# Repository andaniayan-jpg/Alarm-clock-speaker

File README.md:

- This is a custom alarm clock made using a microcontroller, an OLED display, and a rotary encoder.
- The clock allows setting and controlling alarms using the rotary encoder instead of buttons.
- The project includes a custom PCB, 3D-printed enclosure, and firmware.
- I wanted to learn how to design a complete hardware project from scratch.
- I wanted to understand how PCB design, enclosure design, and firmware work together.
- I also wanted to learn how to fix real-world problems like connector height and component placement.
This project is a custom-built alarm clock designed using a microcontroller, an OLED display, and a rotary encoder for user interaction. I created it to learn how a complete hardware project comes together,from PCB 
design and enclosure CAD to basic firmware. While building it, I had to solve practical problems like display mounting height, connector placement, and enclosure fit, which helped me understand real-world hardware
constraints. All design files and code are included so the project can be recreated or modified.

BOM ( bill of materials ), with quantity
1. XIAO ESP32-C3 (1)
2. OLED Display 128x64 (I2C) (1) 
3.  Rotary Encoder (1)
4.  Push Buttons (1)
5.  Speaker-CUI Devices CMR-1206S-67-1 (1)
6.  Battery Holder (1)
7.  Resistors (5)
8.  Capacitors (5)
9.  Custom PCB (1)
   THE FULL LIST OF COMPONENTS WITH PRICE AND QUANTITY IS IN BOM.csv file.

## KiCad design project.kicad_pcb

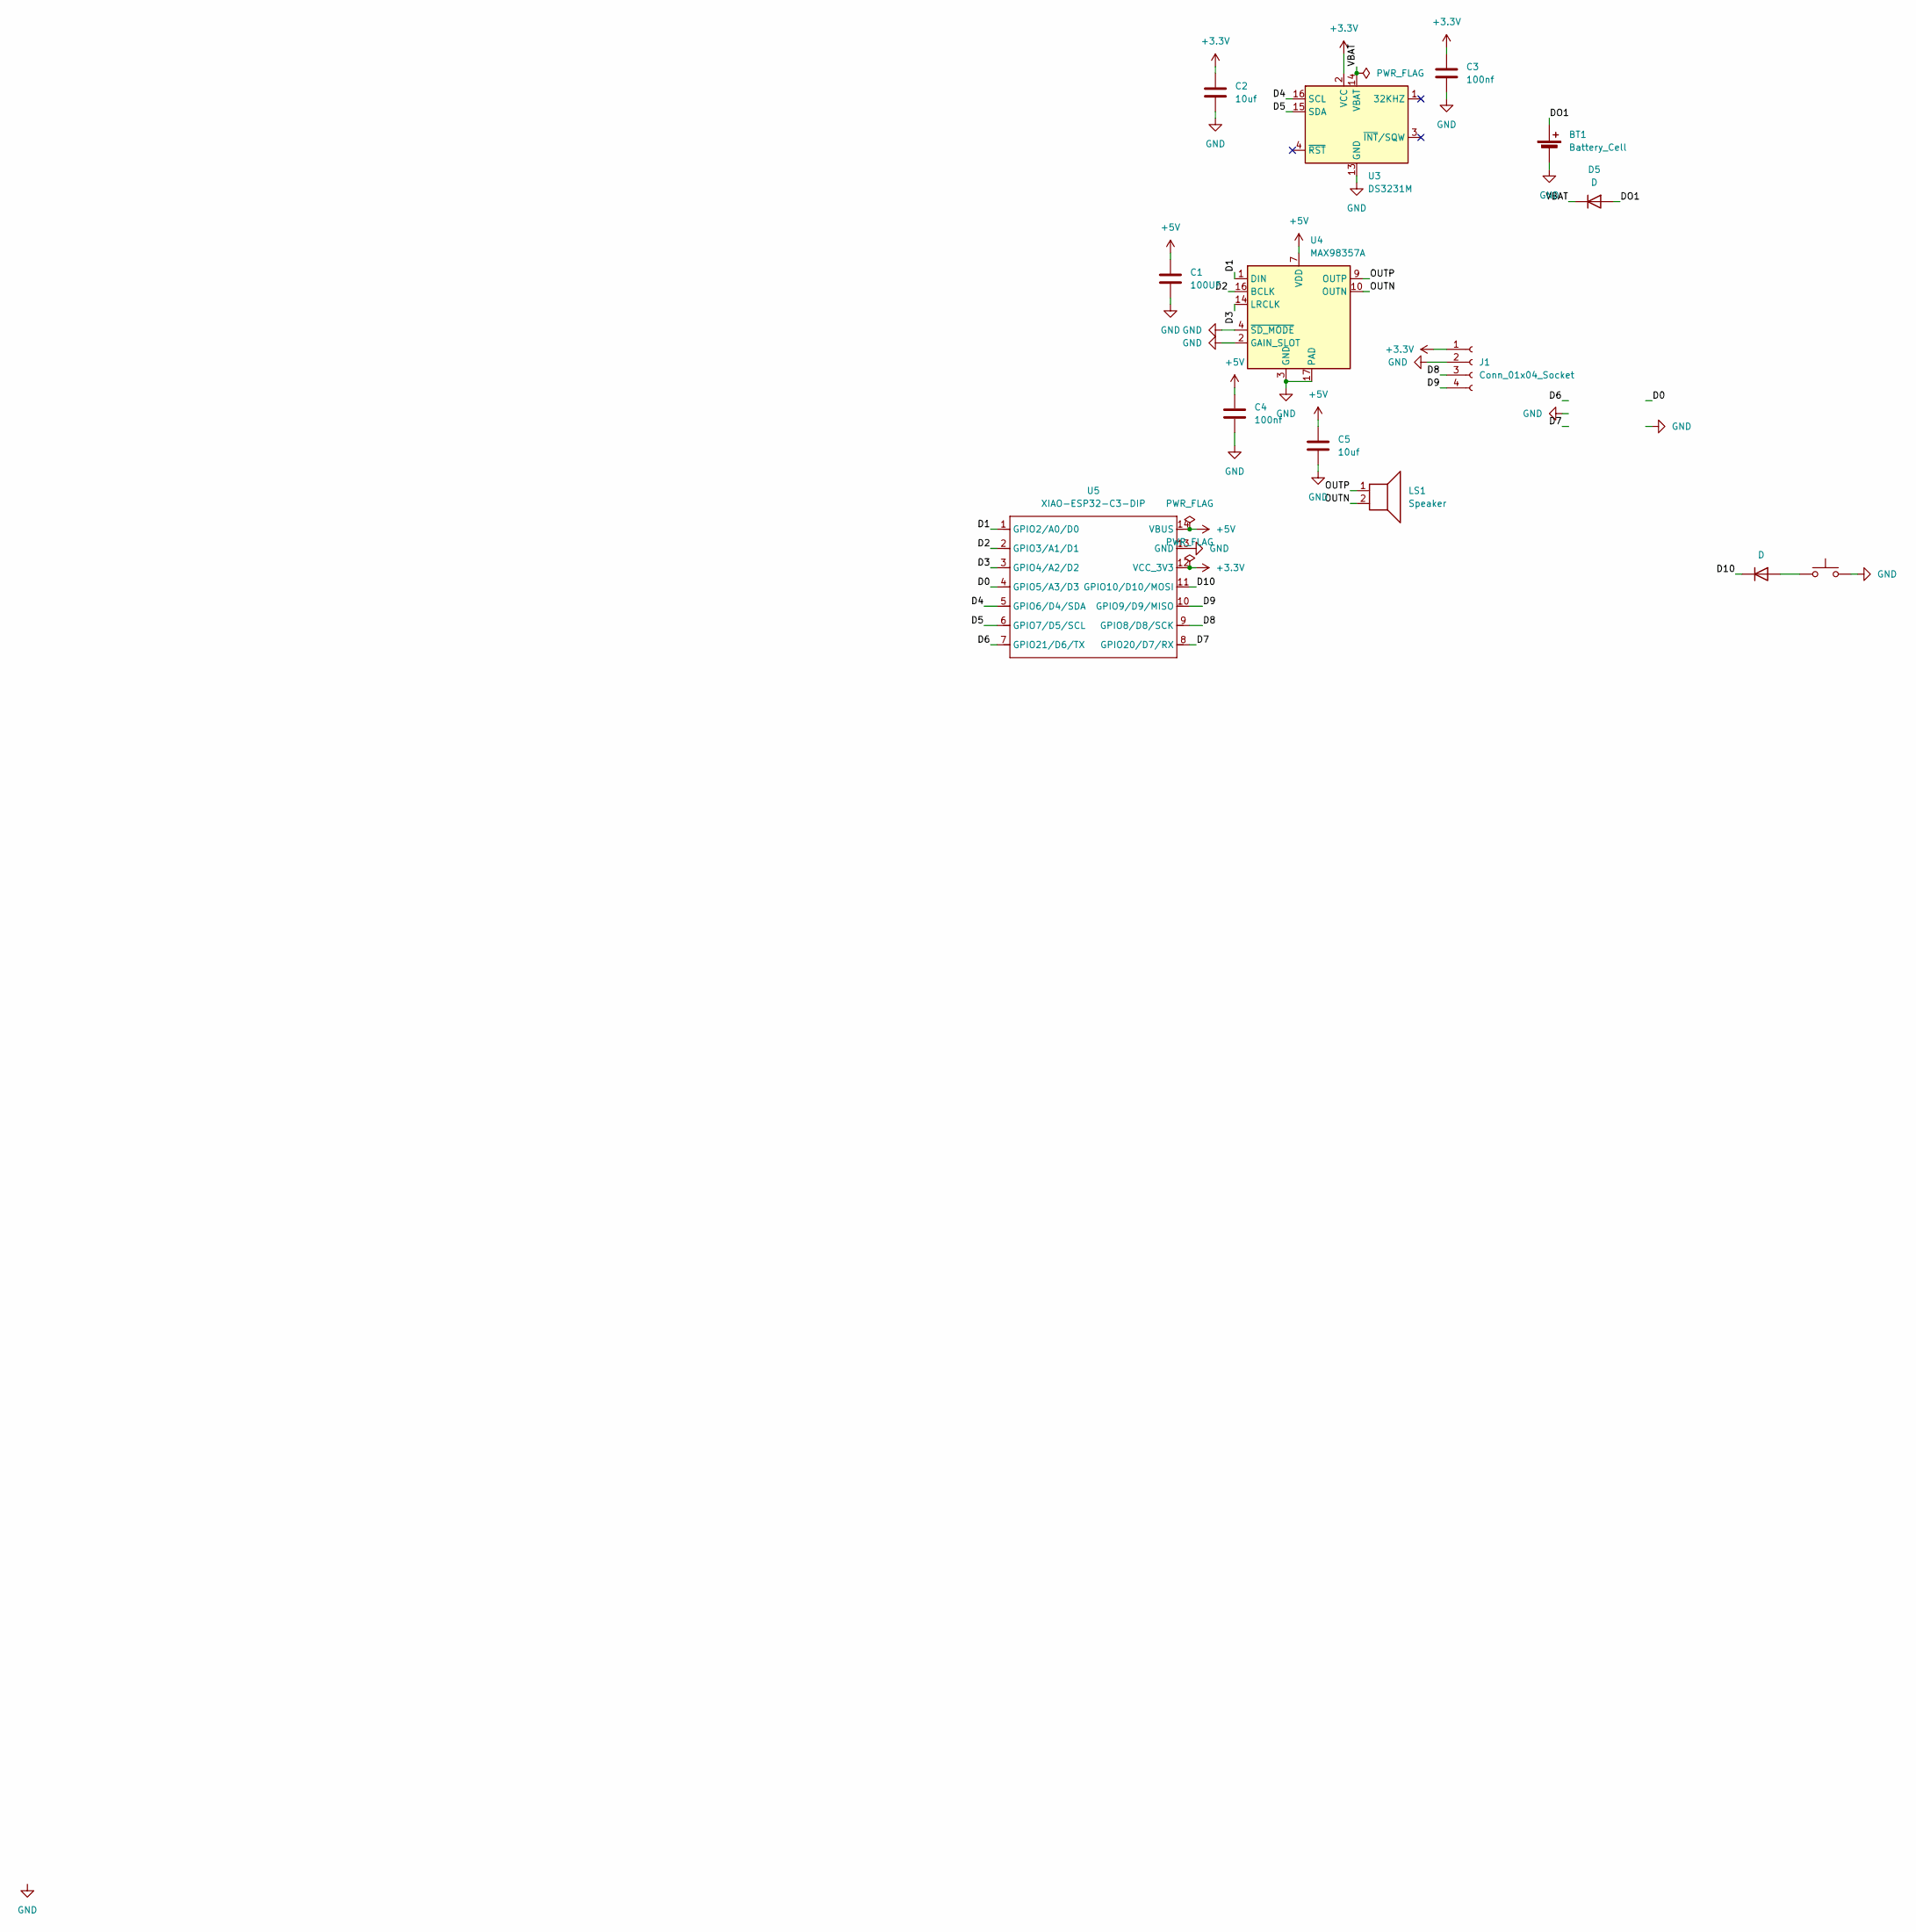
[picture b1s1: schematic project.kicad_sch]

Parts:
BT1: Battery_Cell; BatteryHolder_Keystone_3034_1x20mm
C1: 100UF; C_0805_2012Metric
C2, C5: 10uf; C_0805_2012Metric
C3, C4: 100nf; C_0805_2012Metric
D3, D5: D; D_SOD-123
J1: Conn_01x04_Socket; PinSocket_1x04_P2.54mm_Vertical
LS1: Speaker; Speaker_CUI_CMR-1206S-67
SW3: SW_Push; SW_PUSH_6mm
U3: DS3231M; SOIC-16W_7.5x10.3mm_P1.27mm
U4: MAX98357A; TQFN-16-1EP_3x3mm_P0.5mm_EP1.23x1.23mm
U5: XIAO-ESP32-C3-DIP; MCU_Seeed_ESP32C3

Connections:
+3.3V: C2.1, C3.1, J1.1, U3.2 (VCC), U5.12 (VCC_3V3)
+5V: C1.1, C4.1, C5.1, U4.7 (VDD), U4.8 (VDD), U5.14 (VBUS)
/D0: U5.4 (GPIO5/A3/D3); also elsewhere on the board
/D1: U4.1 (DIN), U5.1 (GPIO2/A0/D0)
/D2: U4.16 (BCLK), U5.2 (GPIO3/A1/D1)
/D3: U4.14 (LRCLK), U5.3 (GPIO4/A2/D2)
/D4: U3.16 (SCL), U5.5 (GPIO6/D4/SDA)
/D5: U3.15 (SDA), U5.6 (GPIO7/D5/SCL)
/D6: U5.7 (GPIO21/D6/TX); also elsewhere on the board
/D7: U5.8 (GPIO20/D7/RX); also elsewhere on the board
/D8: J1.3, U5.9 (GPIO8/D8/SCK)
/D9: J1.4, U5.10 (GPIO9/D9/MISO)
/D10: D3.1 (K), U5.11 (GPIO10/D10/MOSI)
/DO1: BT1.1 (+), D5.2 (A)
/OUTN: LS1.2, U4.10 (OUTN)
/OUTP: LS1.1, U4.9 (OUTP)
/VBAT: D5.1 (K), U3.14 (VBAT)
GND: BT1.2 (-), C1.2, C2.2, C3.2, C4.2, C5.2, J1.2, SW3.2, U3.5 (GND), U3.6 (GND), U3.7 (GND), U3.8 (GND), U3.9 (GND), U3.10 (GND), U3.11 (GND), U3.12 (GND), U3.13 (GND), U4.2 (GAIN_SLOT), U4.3 (GND), U4.4 (~SD_MODE), U4.11 (GND), U4.15 (GND), U4.17 (PAD), U5.13 (GND); also elsewhere on the board
unnamed: D3.2 (A), SW3.1

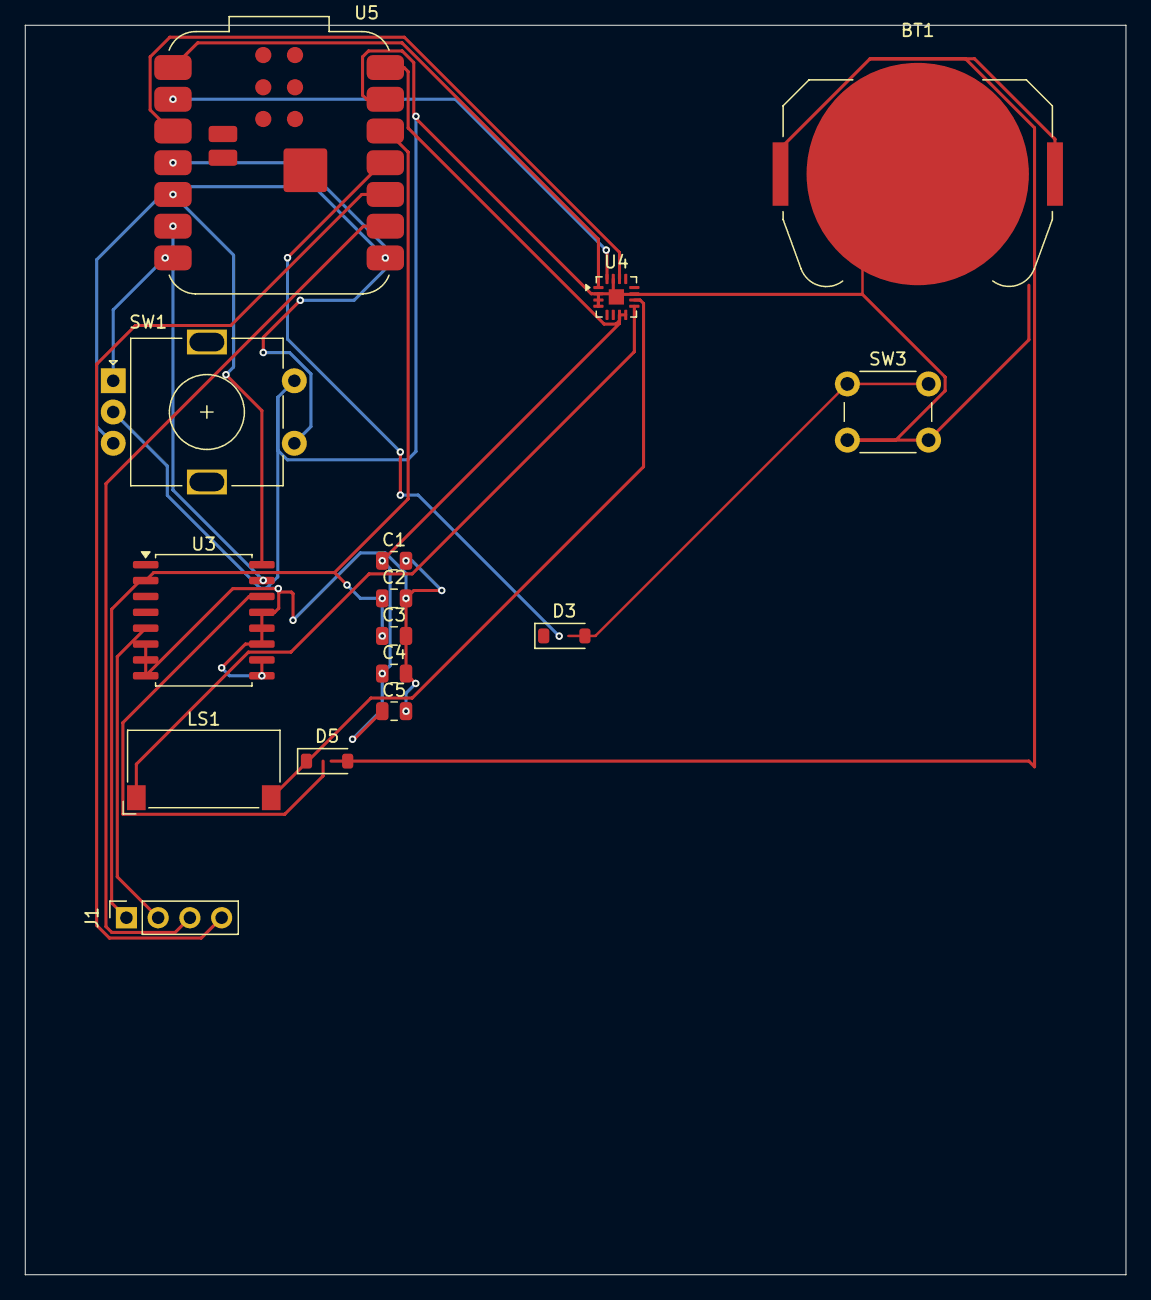
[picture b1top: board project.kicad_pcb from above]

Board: 2 copper layers, 88.1 x 100.0 mm, 15 parts (0 on the bottom side), 19 nets.

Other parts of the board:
SW1: RotaryEncoder_Switch; RotaryEncoder_Alps_EC11E-Switch_Vertical_H20mm

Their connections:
/D0: SW1.S1; also elsewhere on the board
/D6: SW1.A; also elsewhere on the board
/D7: SW1.B; also elsewhere on the board
GND: SW1.C, SW1.S2; also elsewhere on the board

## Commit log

2025-12-22 Add project journal with time tracking and updates
    Documented project progress and time spent on various tasks related to the alarm clock project, including PCB design, enclosure work, and firmware development.
2025-12-22 Add files via upload
    This file containes the STEP for the full assembled model with final structure.
2026-01-28 Add files via upload
    STEP file for fully assembled design
